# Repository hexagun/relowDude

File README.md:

# relowDude
Controller for reflow oven

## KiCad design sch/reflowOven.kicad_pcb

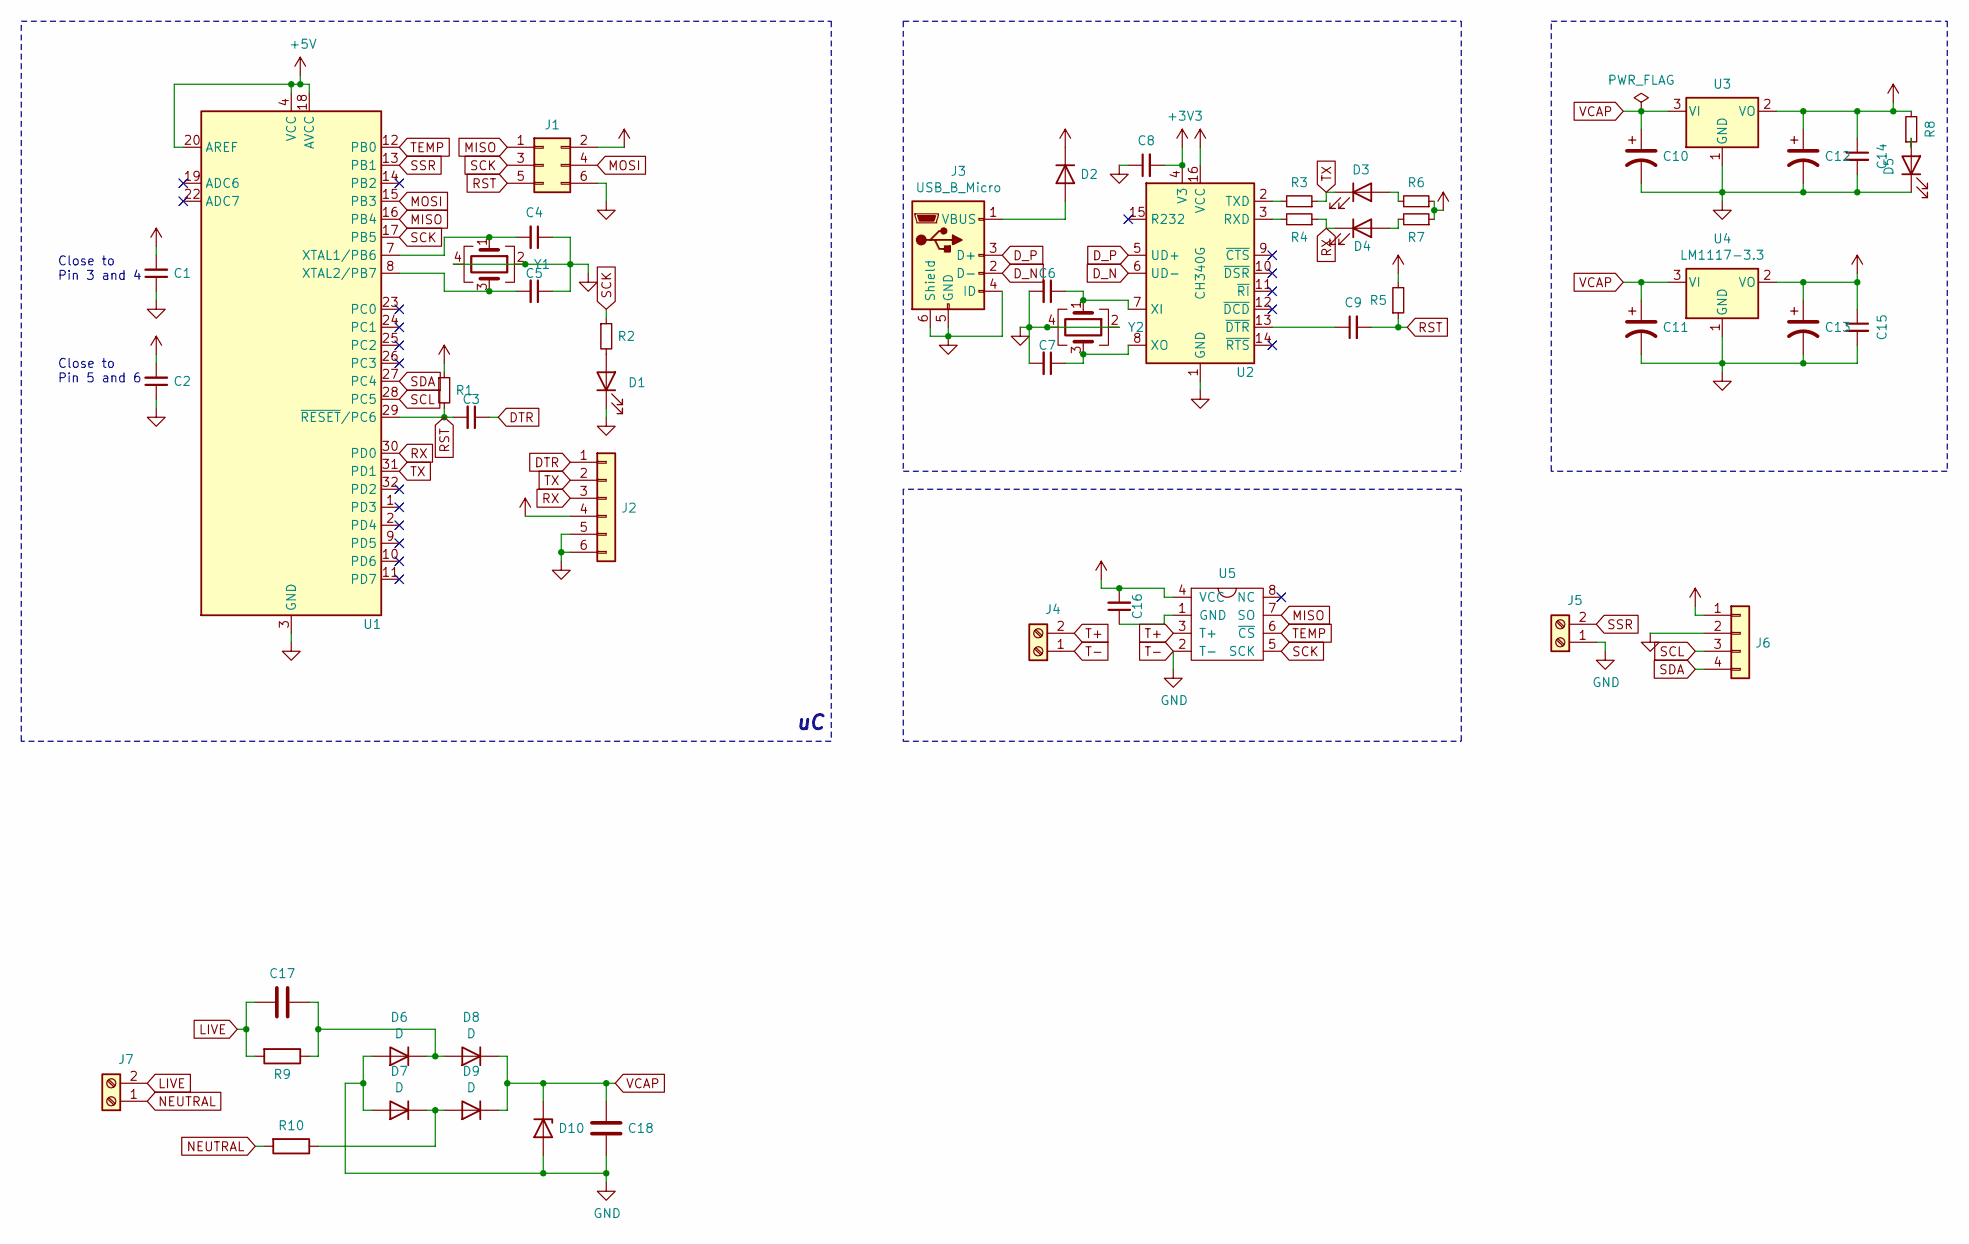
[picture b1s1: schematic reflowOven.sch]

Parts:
C1, C2, C3, C8, C9, C14, C15: 100n; C_0805_2012Metric; JLCPCB C49678
C4, C5, C6, C7: 22p; C_0805_2012Metric; JLCPCB C1804
C10, C11, C12, C13: 10u; CP_EIA-3528-21_Kemet-B; JLCPCB C119050
C16: 0.1u; C_0402_1005Metric; JLCPCB C361198
C17: 2.2u; R475W42205001K; Mouser R475W42205001K
C18: 47u; CP_Elec_6.3x5.9; JLCPCB C311666
D1: LED; LED_0805_2012Metric_Castellated; JLCPCB C84256
D2: 1N4007; D_SOD-323F; JLCPCB C193404
D3: TX; LED_0805_2012Metric_Castellated; JLCPCB C84256
D4: RX; LED_0805_2012Metric_Castellated; JLCPCB C84256
D5: ON; LED_0805_2012Metric_Castellated; JLCPCB C84256
D6, D7, D8, D9: D; D_SMA; JLCPCB C727081
D10: D_Zener; D_MiniMELF; JLCPCB C8061
J1: AVRISP; PinHeader_2x03_P2.54mm_Vertical
J2: UART; PinHeader_1x06_P2.54mm_Vertical
J3: USB_B_Micro; USB_Micro-B_Wuerth_629105150521; JLCPCB C879723
J4: TEMPCONN; PinHeader_1x02_P2.54mm_Vertical
J5: SSRCONN; PinHeader_1x02_P2.54mm_Vertical
J6: DISPLAY; PinHeader_1x04_P2.54mm_Vertical
J7: MAINS; PinHeader_1x02_P2.54mm_Vertical
R1, R5: 10k; R_1206_3216Metric; JLCPCB C17902
R2: 330; R_0603_1608Metric; JLCPCB C23140
R3, R4, R6, R7, R8: 1k; R_0805_2012Metric; JLCPCB C17513
R9: 470k; R_0805_2012Metric_Pad1.20x1.40mm_HandSolder; JLCPCB C17675
R10: 100; R_Axial_DIN0918_L18.0mm_D9.0mm_P25.40mm_Horizontal; Mouser 594-AC05W100R0J
U1: ATmega328P-AU; TQFP-32_7x7mm_P0.8mm; JLCPCB C14877
U2: CH340G; SOIC-16_3.9x9.9mm_P1.27mm; JLCPCB C14267
U3: LM1117-5.0; SOT-223; JLCPCB C131933
U4: LM1117-3.3; SOT-223; JLCPCB C23984
U5: MAX6675; SOIC-8-1EP_3.9x4.9mm_P1.27mm_EP2.29x3mm; JLCPCB C16030
Y1: Crystal_GND24; Crystal_SMD_3225-4Pin_3.2x2.5mm; JLCPCB C13738
Y2: Crystal_GND24; Crystal_SMD_3225-4Pin_3.2x2.5mm; JLCPCB C9002

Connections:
+3V3: C8.2, C13.1, C15.1, U2.4 (V3), U4.2 (VO)
+5V: C1.2, C2.2, C12.1, C14.1, C16.2, D2.1 (K), J1.2, J2.4, J6.1, R1.1, R5.2, R6.1, R7.1, R8.2, U1.4 (VCC), U1.6 (VCC), U1.18 (AVCC), U1.20 (AREF), U2.16 (VCC), U3.2 (VO), U5.4 (VCC)
DTR: C3.1, J2.1
D_N: J3.2 (D-), U2.6 (UD-)
D_P: J3.3 (D+), U2.5 (UD+)
LIVE: C17.2, J7.2, R9.2
MISO: J1.1, U1.16 (PB4), U5.7 (SO)
MOSI: J1.4, U1.15 (PB3)
NEUTRAL: J7.1, R10.2
unnamed: C4.2, U1.7 (XTAL1/PB6), Y1.1
unnamed: C5.2, U1.8 (XTAL2/PB7), Y1.3
unnamed: C6.1, U2.7 (XI), Y2.1
unnamed: C7.1, U2.8 (XO), Y2.3
unnamed: C9.1, U2.13 (~DTR)
unnamed: C16.1, U5.1 (GND)
unnamed: C17.1, D6.1 (K), D8.2 (A), R9.1
unnamed: D1.2 (A), R2.2
unnamed: D2.2 (A), J3.1 (VBUS)
unnamed: D3.2 (A), R6.2
unnamed: D4.2 (A), R7.2
unnamed: D5.2 (A), R8.1
unnamed: D7.1 (K), D9.2 (A), R10.1
unnamed: R3.2, U2.2 (TXD)
unnamed: R4.2, U2.3 (RXD)
RST: C3.2, C9.2, J1.5, R1.2, R5.1, U1.29 (~RESET~/PC6)
RX: D4.1 (K), J2.3, R4.1, U1.30 (PD0)
SCK: J1.3, R2.1, U1.17 (PB5), U5.5 (SCK)
SCL: J6.3, U1.28 (PC5)
SDA: J6.4, U1.27 (PC4)
SSR: J5.2, U1.13 (PB1)
T+: J4.2, U5.3 (T+)
T-: C1.1, C2.1, C4.1, C5.1, C6.2, C7.2, C8.1, C10.2, C11.2, C12.2, C13.2, C14.2, C15.2, C18.2, D1.1 (K), D5.1 (K), D6.2 (A), D7.2 (A), D10.2 (A), J1.6, J2.5, J2.6, J3.4 (ID), J3.5 (GND), J3.6 (Shield), J4.1, J5.1, J6.2, U1.3 (GND), U1.5 (GND), U1.21 (GND), U2.1 (GND), U3.1 (GND), U4.1 (GND), U5.2 (T-), Y1.2, Y1.4, Y2.2, Y2.4
TEMP: U1.12 (PB0), U5.6 (~CS)
TX: D3.1 (K), J2.2, R3.1, U1.31 (PD1)
VCAP: C10.1, C11.1, C18.1, D8.1 (K), D9.1 (K), D10.1 (K), U3.3 (VI), U4.3 (VI)

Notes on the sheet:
Close to Pin 3 and 4
Close to Pin 5 and 6

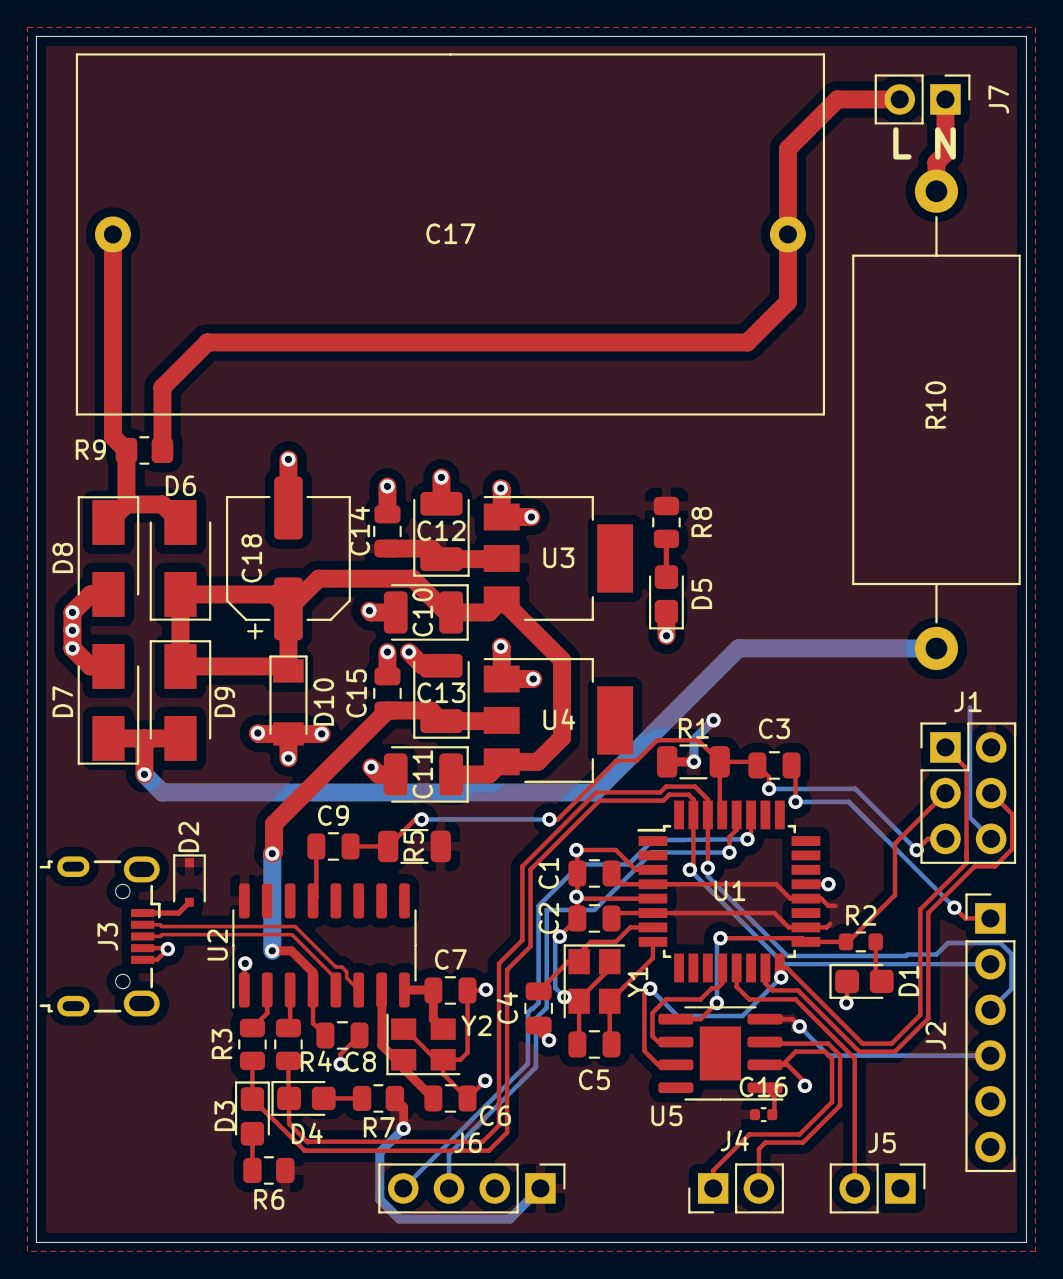
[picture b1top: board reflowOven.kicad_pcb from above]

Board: 2 copper layers, 55.0 x 67.0 mm, 52 parts (0 on the bottom side), 35 nets.
